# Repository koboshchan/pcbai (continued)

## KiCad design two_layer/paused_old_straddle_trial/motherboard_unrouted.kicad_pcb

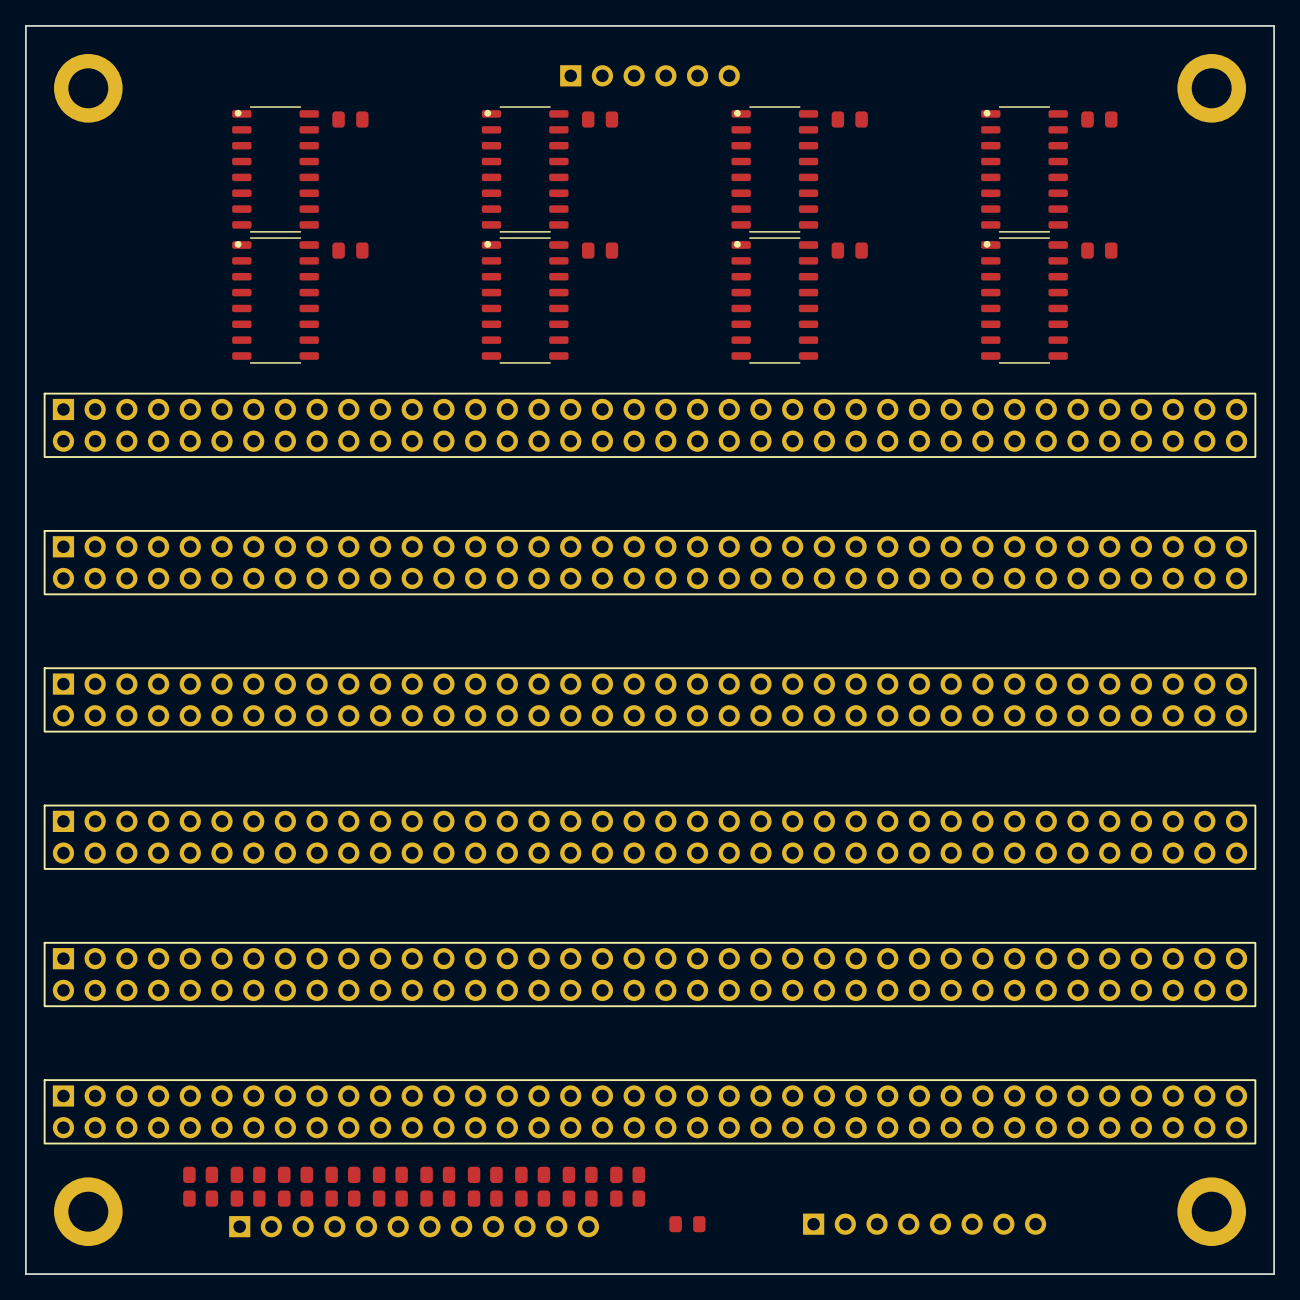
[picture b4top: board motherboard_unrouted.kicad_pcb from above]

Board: 2 copper layers, 100.0 x 100.0 mm, 50 parts (0 on the bottom side), 133 nets, no tracks yet.

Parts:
C_SR1, C_SR2, C_SR3, C_SR4, C_SR5, C_SR6, C_SR7, C_SR8: 0.1uF; C_0805_2012Metric
H1, H2, H3, H4: MountingHole; MountingHole_3.2mm_M3_Pad
J_MCU_SCORES: Scores_DIV_3V3_Out; PinHeader_1x12_P2.54mm_Vertical
J_MCU_SPI: MCU_SPI_In; PinHeader_1x06_P2.54mm_Vertical
J_PWR_IN: Main_Power_In; PinHeader_1x08_P2.54mm_Vertical
J_SLOT0: Slot0: DC1A (L1 Neurons 0..3); PinSocket_2x38_P2.54mm_Vertical
J_SLOT1: Slot1: DC1B (L1 Neurons 4..7); PinSocket_2x38_P2.54mm_Vertical
J_SLOT2: Slot2: DC1C (L1 Neurons 8..11); PinSocket_2x38_P2.54mm_Vertical
J_SLOT3: Slot3: DC1D (L1 Neurons 12..15); PinSocket_2x38_P2.54mm_Vertical
J_SLOT4: Slot4: DC2 (16x Active Precision ReLU); PinSocket_2x38_P2.54mm_Vertical
J_SLOT5: Slot5: DC3 (L2 Weights + 10-Way WTA); PinSocket_2x38_P2.54mm_Vertical
R_BOT_0, R_BOT_1, R_BOT_2, R_BOT_3, R_BOT_4, R_BOT_5, R_BOT_6, R_BOT_7, R_BOT_8, R_BOT_9: 20k; R_0805_2012Metric
R_PWR5: 0R; R_0805_2012Metric
R_TOP_0, R_TOP_1, R_TOP_2, R_TOP_3, R_TOP_4, R_TOP_5, R_TOP_6, R_TOP_7, R_TOP_8, R_TOP_9: 10k; R_0805_2012Metric
U_SR1, U_SR2, U_SR3, U_SR4, U_SR5, U_SR6, U_SR7, U_SR8: 74HC595D; SOIC-16_3.9x9.9mm_P1.27mm

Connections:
+5V: C_SR1.1, C_SR2.1, C_SR3.1, C_SR4.1, C_SR5.1, C_SR6.1, C_SR7.1, C_SR8.1, J_MCU_SPI.1, R_PWR5.2, U_SR1.10, U_SR1.16, U_SR2.10, U_SR2.16, U_SR3.10, U_SR3.16, U_SR4.10, U_SR4.16, U_SR5.10, U_SR5.16, U_SR6.10, U_SR6.16, U_SR7.10, U_SR7.16, U_SR8.10, U_SR8.16
+5V_REF: J_PWR_IN.7, J_SLOT0.B35, J_SLOT1.B35, J_SLOT2.B35, J_SLOT3.B35, J_SLOT4.B35, J_SLOT5.B35, R_PWR5.1
+12V: J_PWR_IN.1, J_PWR_IN.2, J_SLOT0.B33, J_SLOT0.B34, J_SLOT1.B33, J_SLOT1.B34, J_SLOT2.B33, J_SLOT2.B34, J_SLOT3.B33, J_SLOT3.B34, J_SLOT4.B33, J_SLOT4.B34, J_SLOT5.B33, J_SLOT5.B34
-5V_REF: J_PWR_IN.8, J_SLOT0.B36, J_SLOT1.B36, J_SLOT2.B36, J_SLOT3.B36, J_SLOT4.B36, J_SLOT5.B36
-12V: J_PWR_IN.5, J_PWR_IN.6, J_SLOT0.B37, J_SLOT0.B38, J_SLOT1.B37, J_SLOT1.B38, J_SLOT2.B37, J_SLOT2.B38, J_SLOT3.B37, J_SLOT3.B38, J_SLOT4.B37, J_SLOT4.B38, J_SLOT5.B37, J_SLOT5.B38
ACT_0: J_SLOT4.B1, J_SLOT5.A1
ACT_1: J_SLOT4.B2, J_SLOT5.A2
ACT_2: J_SLOT4.B3, J_SLOT5.A3
ACT_3: J_SLOT4.B4, J_SLOT5.A4
ACT_4: J_SLOT4.B5, J_SLOT5.A5
ACT_5: J_SLOT4.B6, J_SLOT5.A6
ACT_6: J_SLOT4.B7, J_SLOT5.A7
ACT_7: J_SLOT4.B8, J_SLOT5.A8
ACT_8: J_SLOT4.B9, J_SLOT5.A9
ACT_9: J_SLOT4.B10, J_SLOT5.A10
ACT_10: J_SLOT4.B11, J_SLOT5.A11
ACT_11: J_SLOT4.B12, J_SLOT5.A12
ACT_12: J_SLOT4.B13, J_SLOT5.A13
ACT_13: J_SLOT4.B14, J_SLOT5.A14
ACT_14: J_SLOT4.B15, J_SLOT5.A15
ACT_15: J_SLOT4.B16, J_SLOT5.A16
GND: C_SR1.2, C_SR2.2, C_SR3.2, C_SR4.2, C_SR5.2, C_SR6.2, C_SR7.2, C_SR8.2, H1.1, H2.1, H3.1, H4.1, J_MCU_SCORES.11, J_MCU_SCORES.12, J_MCU_SPI.2, J_PWR_IN.3, J_PWR_IN.4, J_SLOT0.A37, J_SLOT0.A38, J_SLOT1.A37, J_SLOT1.A38, J_SLOT2.A37, J_SLOT2.A38, J_SLOT3.A37, J_SLOT3.A38, J_SLOT4.A17, J_SLOT4.A18, J_SLOT4.A19, J_SLOT4.A20, J_SLOT4.A21, J_SLOT4.A22, J_SLOT4.A23, J_SLOT4.A24, J_SLOT4.A25, J_SLOT4.A26, J_SLOT4.A27, J_SLOT4.A28, J_SLOT4.A29, J_SLOT4.A30, J_SLOT4.A31, J_SLOT4.A32, J_SLOT4.A33, J_SLOT4.A34, J_SLOT4.A35, J_SLOT4.A36, J_SLOT4.A37, J_SLOT4.A38, J_SLOT4.B17, J_SLOT4.B18, J_SLOT4.B19, J_SLOT4.B20, J_SLOT4.B21, J_SLOT4.B22, J_SLOT4.B23, J_SLOT4.B24, J_SLOT4.B25, J_SLOT4.B26, J_SLOT4.B27, J_SLOT4.B28, J_SLOT4.B29, J_SLOT4.B30, J_SLOT4.B31, J_SLOT4.B32, J_SLOT5.A17, J_SLOT5.A18, J_SLOT5.A19, J_SLOT5.A20, J_SLOT5.A21, J_SLOT5.A22, J_SLOT5.A23, J_SLOT5.A24, J_SLOT5.A25, J_SLOT5.A26, J_SLOT5.A27, J_SLOT5.A28, J_SLOT5.A29, J_SLOT5.A30, J_SLOT5.A31, J_SLOT5.A32, J_SLOT5.A33, J_SLOT5.A34, J_SLOT5.A35, J_SLOT5.A36, J_SLOT5.A37, J_SLOT5.A38, J_SLOT5.B11, J_SLOT5.B12, J_SLOT5.B13, J_SLOT5.B14, J_SLOT5.B15, J_SLOT5.B16, J_SLOT5.B17, J_SLOT5.B18, J_SLOT5.B19, J_SLOT5.B20, J_SLOT5.B21, J_SLOT5.B22, J_SLOT5.B23, J_SLOT5.B24, J_SLOT5.B25, J_SLOT5.B26, J_SLOT5.B27, J_SLOT5.B28, J_SLOT5.B29, J_SLOT5.B30, J_SLOT5.B31, J_SLOT5.B32, R_BOT_0.1, R_BOT_1.1, R_BOT_2.1, R_BOT_3.1, R_BOT_4.1, R_BOT_5.1, R_BOT_6.1, R_BOT_7.1, R_BOT_8.1, R_BOT_9.1, U_SR1.8, U_SR2.8, U_SR3.8, U_SR4.8, U_SR5.8, U_SR6.8, U_SR7.8, U_SR8.8
IN_0: J_SLOT0.A1, J_SLOT1.A1, J_SLOT2.A1, J_SLOT3.A1, U_SR1.15
IN_1: J_SLOT0.A2, J_SLOT1.A2, J_SLOT2.A2, J_SLOT3.A2, U_SR1.1
IN_2: J_SLOT0.A3, J_SLOT1.A3, J_SLOT2.A3, J_SLOT3.A3, U_SR1.2
IN_3: J_SLOT0.A4, J_SLOT1.A4, J_SLOT2.A4, J_SLOT3.A4, U_SR1.3
IN_4: J_SLOT0.A5, J_SLOT1.A5, J_SLOT2.A5, J_SLOT3.A5, U_SR1.4
IN_5: J_SLOT0.A6, J_SLOT1.A6, J_SLOT2.A6, J_SLOT3.A6, U_SR1.5
IN_6: J_SLOT0.A7, J_SLOT1.A7, J_SLOT2.A7, J_SLOT3.A7, U_SR1.6
IN_7: J_SLOT0.A8, J_SLOT1.A8, J_SLOT2.A8, J_SLOT3.A8, U_SR1.7
IN_8: J_SLOT0.A9, J_SLOT1.A9, J_SLOT2.A9, J_SLOT3.A9, U_SR2.15
IN_9: J_SLOT0.A10, J_SLOT1.A10, J_SLOT2.A10, J_SLOT3.A10, U_SR2.1
IN_10: J_SLOT0.A11, J_SLOT1.A11, J_SLOT2.A11, J_SLOT3.A11, U_SR2.2
IN_11: J_SLOT0.A12, J_SLOT1.A12, J_SLOT2.A12, J_SLOT3.A12, U_SR2.3
IN_12: J_SLOT0.A13, J_SLOT1.A13, J_SLOT2.A13, J_SLOT3.A13, U_SR2.4
IN_13: J_SLOT0.A14, J_SLOT1.A14, J_SLOT2.A14, J_SLOT3.A14, U_SR2.5
IN_14: J_SLOT0.A15, J_SLOT1.A15, J_SLOT2.A15, J_SLOT3.A15, U_SR2.6
IN_15: J_SLOT0.A16, J_SLOT1.A16, J_SLOT2.A16, J_SLOT3.A16, U_SR2.7
IN_16: J_SLOT0.A17, J_SLOT1.A17, J_SLOT2.A17, J_SLOT3.A17, U_SR3.15
IN_17: J_SLOT0.A18, J_SLOT1.A18, J_SLOT2.A18, J_SLOT3.A18, U_SR3.1
IN_18: J_SLOT0.A19, J_SLOT1.A19, J_SLOT2.A19, J_SLOT3.A19, U_SR3.2
IN_19: J_SLOT0.A20, J_SLOT1.A20, J_SLOT2.A20, J_SLOT3.A20, U_SR3.3
IN_20: J_SLOT0.A21, J_SLOT1.A21, J_SLOT2.A21, J_SLOT3.A21, U_SR3.4
IN_21: J_SLOT0.A22, J_SLOT1.A22, J_SLOT2.A22, J_SLOT3.A22, U_SR3.5
IN_22: J_SLOT0.A23, J_SLOT1.A23, J_SLOT2.A23, J_SLOT3.A23, U_SR3.6
IN_23: J_SLOT0.A24, J_SLOT1.A24, J_SLOT2.A24, J_SLOT3.A24, U_SR3.7
IN_24: J_SLOT0.A25, J_SLOT1.A25, J_SLOT2.A25, J_SLOT3.A25, U_SR4.15
IN_25: J_SLOT0.A26, J_SLOT1.A26, J_SLOT2.A26, J_SLOT3.A26, U_SR4.1
IN_26: J_SLOT0.A27, J_SLOT1.A27, J_SLOT2.A27, J_SLOT3.A27, U_SR4.2
IN_27: J_SLOT0.A28, J_SLOT1.A28, J_SLOT2.A28, J_SLOT3.A28, U_SR4.3
IN_28: J_SLOT0.A29, J_SLOT1.A29, J_SLOT2.A29, J_SLOT3.A29, U_SR4.4
IN_29: J_SLOT0.A30, J_SLOT1.A30, J_SLOT2.A30, J_SLOT3.A30, U_SR4.5
IN_30: J_SLOT0.A31, J_SLOT1.A31, J_SLOT2.A31, J_SLOT3.A31, U_SR4.6
IN_31: J_SLOT0.A32, J_SLOT1.A32, J_SLOT2.A32, J_SLOT3.A32, U_SR4.7
IN_32: J_SLOT0.B1, J_SLOT1.B1, J_SLOT2.B1, J_SLOT3.B1, U_SR8.15
IN_33: J_SLOT0.B2, J_SLOT1.B2, J_SLOT2.B2, J_SLOT3.B2, U_SR8.1
IN_34: J_SLOT0.B3, J_SLOT1.B3, J_SLOT2.B3, J_SLOT3.B3, U_SR8.2
IN_35: J_SLOT0.B4, J_SLOT1.B4, J_SLOT2.B4, J_SLOT3.B4, U_SR8.3
IN_36: J_SLOT0.B5, J_SLOT1.B5, J_SLOT2.B5, J_SLOT3.B5, U_SR8.4
IN_37: J_SLOT0.B6, J_SLOT1.B6, J_SLOT2.B6, J_SLOT3.B6, U_SR8.5
IN_38: J_SLOT0.B7, J_SLOT1.B7, J_SLOT2.B7, J_SLOT3.B7, U_SR8.6
IN_39: J_SLOT0.B8, J_SLOT1.B8, J_SLOT2.B8, J_SLOT3.B8, U_SR8.7
IN_40: J_SLOT0.B9, J_SLOT1.B9, J_SLOT2.B9, J_SLOT3.B9, U_SR7.15
IN_41: J_SLOT0.B10, J_SLOT1.B10, J_SLOT2.B10, J_SLOT3.B10, U_SR7.1
IN_42: J_SLOT0.B11, J_SLOT1.B11, J_SLOT2.B11, J_SLOT3.B11, U_SR7.2
IN_43: J_SLOT0.B12, J_SLOT1.B12, J_SLOT2.B12, J_SLOT3.B12, U_SR7.3
IN_44: J_SLOT0.B13, J_SLOT1.B13, J_SLOT2.B13, J_SLOT3.B13, U_SR7.4
IN_45: J_SLOT0.B14, J_SLOT1.B14, J_SLOT2.B14, J_SLOT3.B14, U_SR7.5
IN_46: J_SLOT0.B15, J_SLOT1.B15, J_SLOT2.B15, J_SLOT3.B15, U_SR7.6
IN_47: J_SLOT0.B16, J_SLOT1.B16, J_SLOT2.B16, J_SLOT3.B16, U_SR7.7
IN_48: J_SLOT0.B17, J_SLOT1.B17, J_SLOT2.B17, J_SLOT3.B17, U_SR6.15
IN_49: J_SLOT0.B18, J_SLOT1.B18, J_SLOT2.B18, J_SLOT3.B18, U_SR6.1
IN_50: J_SLOT0.B19, J_SLOT1.B19, J_SLOT2.B19, J_SLOT3.B19, U_SR6.2
IN_51: J_SLOT0.B20, J_SLOT1.B20, J_SLOT2.B20, J_SLOT3.B20, U_SR6.3
IN_52: J_SLOT0.B21, J_SLOT1.B21, J_SLOT2.B21, J_SLOT3.B21, U_SR6.4
IN_53: J_SLOT0.B22, J_SLOT1.B22, J_SLOT2.B22, J_SLOT3.B22, U_SR6.5
IN_54: J_SLOT0.B23, J_SLOT1.B23, J_SLOT2.B23, J_SLOT3.B23, U_SR6.6
IN_55: J_SLOT0.B24, J_SLOT1.B24, J_SLOT2.B24, J_SLOT3.B24, U_SR6.7
IN_56: J_SLOT0.B25, J_SLOT1.B25, J_SLOT2.B25, J_SLOT3.B25, U_SR5.15
IN_57: J_SLOT0.B26, J_SLOT1.B26, J_SLOT2.B26, J_SLOT3.B26, U_SR5.1
IN_58: J_SLOT0.B27, J_SLOT1.B27, J_SLOT2.B27, J_SLOT3.B27, U_SR5.2
IN_59: J_SLOT0.B28, J_SLOT1.B28, J_SLOT2.B28, J_SLOT3.B28, U_SR5.3
IN_60: J_SLOT0.B29, J_SLOT1.B29, J_SLOT2.B29, J_SLOT3.B29, U_SR5.4
IN_61: J_SLOT0.B30, J_SLOT1.B30, J_SLOT2.B30, J_SLOT3.B30, U_SR5.5
IN_62: J_SLOT0.B31, J_SLOT1.B31, J_SLOT2.B31, J_SLOT3.B31, U_SR5.6
IN_63: J_SLOT0.B32, J_SLOT1.B32, J_SLOT2.B32, J_SLOT3.B32, U_SR5.7
SCORE_0: J_SLOT5.B1, R_TOP_0.1
SCORE_1: J_SLOT5.B2, R_TOP_1.1
SCORE_2: J_SLOT5.B3, R_TOP_2.1
SCORE_3: J_SLOT5.B4, R_TOP_3.1
SCORE_4: J_SLOT5.B5, R_TOP_4.1
SCORE_5: J_SLOT5.B6, R_TOP_5.1
SCORE_6: J_SLOT5.B7, R_TOP_6.1
SCORE_7: J_SLOT5.B8, R_TOP_7.1
SCORE_8: J_SLOT5.B9, R_TOP_8.1
SCORE_9: J_SLOT5.B10, R_TOP_9.1
SCORE_DIV_0: J_MCU_SCORES.1, R_BOT_0.2, R_TOP_0.2
SCORE_DIV_1: J_MCU_SCORES.2, R_BOT_1.2, R_TOP_1.2
SCORE_DIV_2: J_MCU_SCORES.3, R_BOT_2.2, R_TOP_2.2
SCORE_DIV_3: J_MCU_SCORES.4, R_BOT_3.2, R_TOP_3.2
SCORE_DIV_4: J_MCU_SCORES.5, R_BOT_4.2, R_TOP_4.2
SCORE_DIV_5: J_MCU_SCORES.6, R_BOT_5.2, R_TOP_5.2
SCORE_DIV_6: J_MCU_SCORES.7, R_BOT_6.2, R_TOP_6.2
SCORE_DIV_7: J_MCU_SCORES.8, R_BOT_7.2, R_TOP_7.2
SCORE_DIV_8: J_MCU_SCORES.9, R_BOT_8.2, R_TOP_8.2
SCORE_DIV_9: J_MCU_SCORES.10, R_BOT_9.2, R_TOP_9.2
SPI_LATCH: J_MCU_SPI.5, U_SR1.12, U_SR2.12, U_SR3.12, U_SR4.12, U_SR5.12, U_SR6.12, U_SR7.12, U_SR8.12
SPI_MOSI: J_MCU_SPI.3, U_SR1.14
SPI_OE: J_MCU_SPI.6, U_SR1.13, U_SR2.13, U_SR3.13, U_SR4.13, U_SR5.13, U_SR6.13, U_SR7.13, U_SR8.13
SPI_SCK: J_MCU_SPI.4, U_SR1.11, U_SR2.11, U_SR3.11, U_SR4.11, U_SR5.11, U_SR6.11, U_SR7.11, U_SR8.11
SR_CHAIN_1: U_SR1.9, U_SR2.14
SR_CHAIN_2: U_SR2.9, U_SR3.14
SR_CHAIN_3: U_SR3.9, U_SR4.14
SR_CHAIN_4: U_SR4.9, U_SR5.14
SR_CHAIN_5: U_SR5.9, U_SR6.14
SR_CHAIN_6: U_SR6.9, U_SR7.14
SR_CHAIN_7: U_SR7.9, U_SR8.14
V_SUM_0: J_SLOT0.A33, J_SLOT4.A1
V_SUM_1: J_SLOT0.A34, J_SLOT4.A2
V_SUM_2: J_SLOT0.A35, J_SLOT4.A3
V_SUM_3: J_SLOT0.A36, J_SLOT4.A4
V_SUM_4: J_SLOT1.A33, J_SLOT4.A5
V_SUM_5: J_SLOT1.A34, J_SLOT4.A6
V_SUM_6: J_SLOT1.A35, J_SLOT4.A7
V_SUM_7: J_SLOT1.A36, J_SLOT4.A8
V_SUM_8: J_SLOT2.A33, J_SLOT4.A9
V_SUM_9: J_SLOT2.A34, J_SLOT4.A10
V_SUM_10: J_SLOT2.A35, J_SLOT4.A11
V_SUM_11: J_SLOT2.A36, J_SLOT4.A12
V_SUM_12: J_SLOT3.A33, J_SLOT4.A13
V_SUM_13: J_SLOT3.A34, J_SLOT4.A14
V_SUM_14: J_SLOT3.A35, J_SLOT4.A15
V_SUM_15: J_SLOT3.A36, J_SLOT4.A16
